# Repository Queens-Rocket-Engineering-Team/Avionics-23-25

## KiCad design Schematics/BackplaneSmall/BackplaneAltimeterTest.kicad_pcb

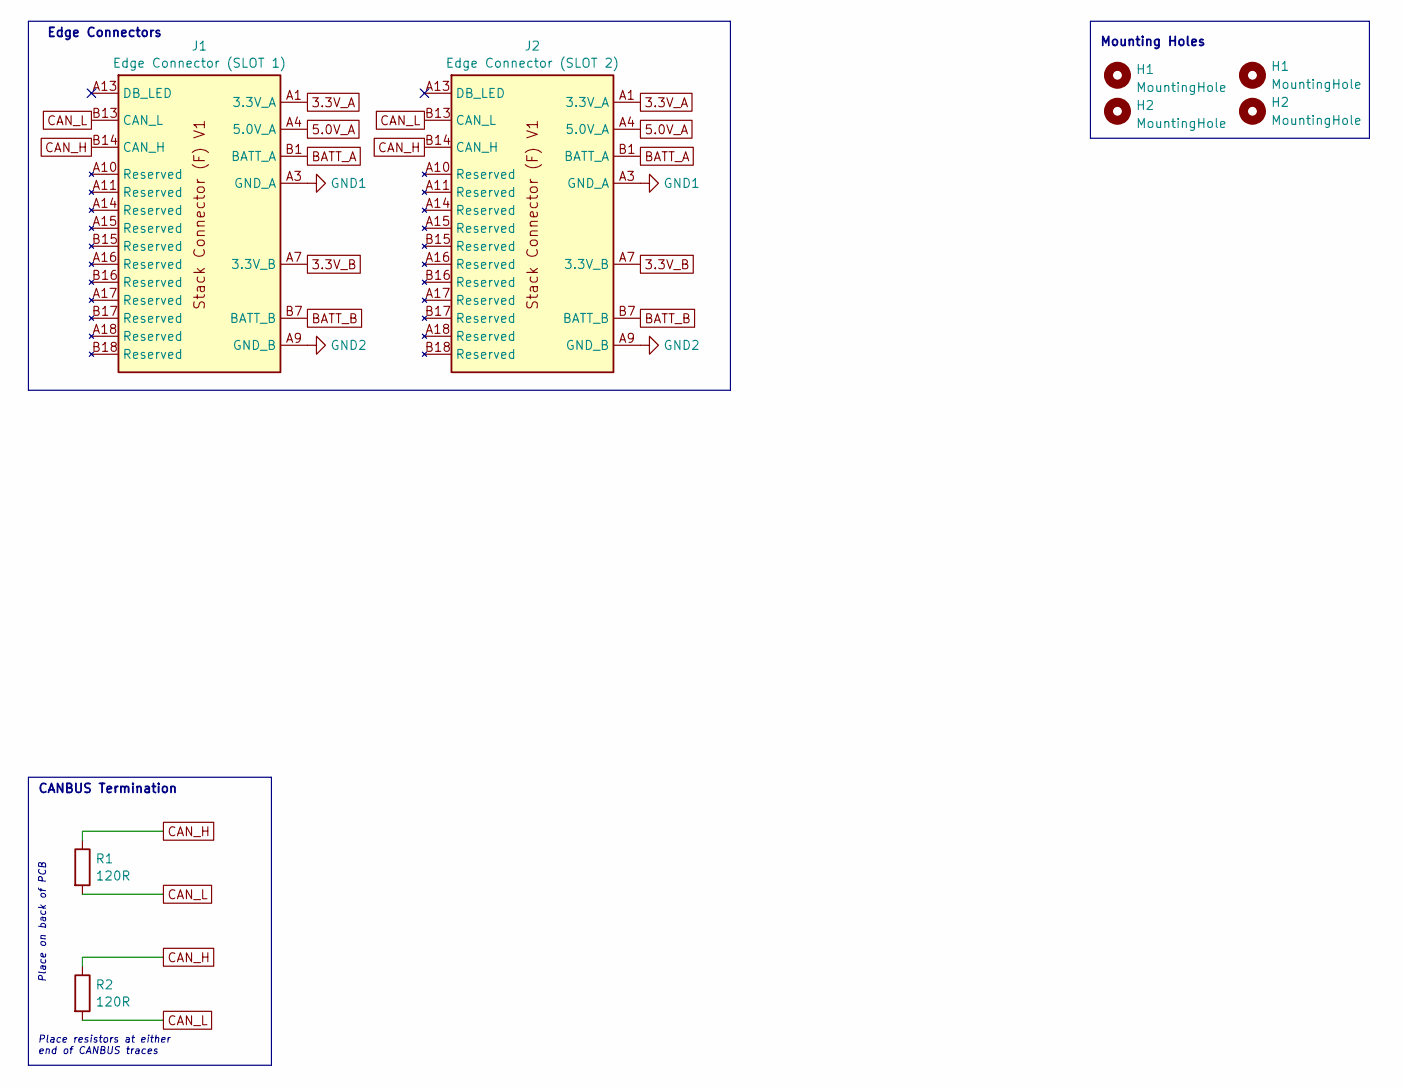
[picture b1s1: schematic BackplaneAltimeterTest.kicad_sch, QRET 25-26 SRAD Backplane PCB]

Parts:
H1, H2: MountingHole; MountingHole_3.2mm_M3_ISO14580_Pad
J1: Edge Connector (SLOT 1); AMPHENOL_10018784-10210TLF; Digikey 609-2029-ND
J2: Edge Connector (SLOT 2); AMPHENOL_10018784-10210TLF; Digikey 609-2029-ND
R1, R2: 120R; R_0805_2012Metric_Pad1.20x1.40mm_HandSolder; Digikey A129738CT-ND

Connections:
3.3V_A: J1.A1 (3.3V_A), J1.A2 (3.3V_A), J2.A1 (3.3V_A), J2.A2 (3.3V_A)
3.3V_B: J1.A7 (3.3V_B), J1.A8 (3.3V_B), J2.A7 (3.3V_B), J2.A8 (3.3V_B)
5.0V_A: J1.A4 (5.0V_A), J1.A5 (5.0V_A), J2.A4 (5.0V_A), J2.A5 (5.0V_A)
BATT_A: J1.B1 (BATT_A), J1.B2 (BATT_A), J1.B3 (BATT_A), J2.B1 (BATT_A), J2.B2 (BATT_A), J2.B3 (BATT_A)
BATT_B: J1.B7 (BATT_B), J1.B8 (BATT_B), J1.B9 (BATT_B), J2.B7 (BATT_B), J2.B8 (BATT_B), J2.B9 (BATT_B)
CAN_H: J1.B14 (CAN_H), J2.B14 (CAN_H), R1.1, R2.1
CAN_L: J1.B13 (CAN_L), J2.B13 (CAN_L), R1.2, R2.2
GND1: J1.A3 (GND_A), J1.A6 (GND_A), J1.B4 (GND_A), J1.B5 (GND_A), J1.B6 (GND_A), J2.A3 (GND_A), J2.A6 (GND_A), J2.B4 (GND_A), J2.B5 (GND_A), J2.B6 (GND_A)
GND2: J1.A9 (GND_B), J1.A12 (GND_B), J1.B10 (GND_B), J1.B11 (GND_B), J1.B12 (GND_B), J2.A9 (GND_B), J2.A12 (GND_B), J2.B10 (GND_B), J2.B11 (GND_B), J2.B12 (GND_B)

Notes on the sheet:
CANBUS Termination
Place resistors at either end of CANBUS traces
Mounting Holes
Edge Connectors
Place on back of PCB

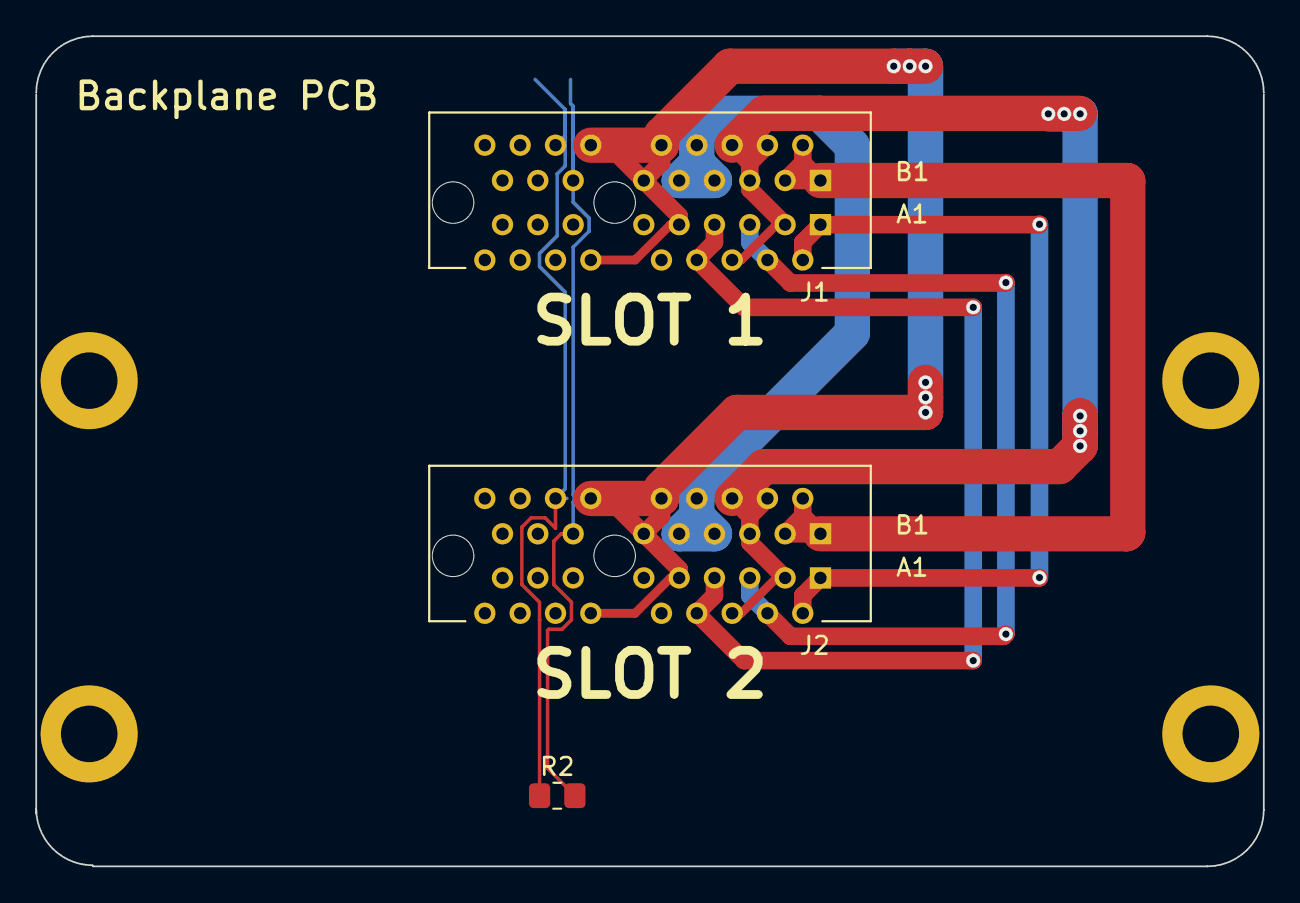
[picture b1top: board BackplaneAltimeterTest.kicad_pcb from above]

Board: 2 copper layers, 69.5 x 47.0 mm, 8 parts (1 on the bottom side), 9 nets.

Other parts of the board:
H3, H4: MountingHole; MountingHole_3.2mm_M3_ISO14580_Pad

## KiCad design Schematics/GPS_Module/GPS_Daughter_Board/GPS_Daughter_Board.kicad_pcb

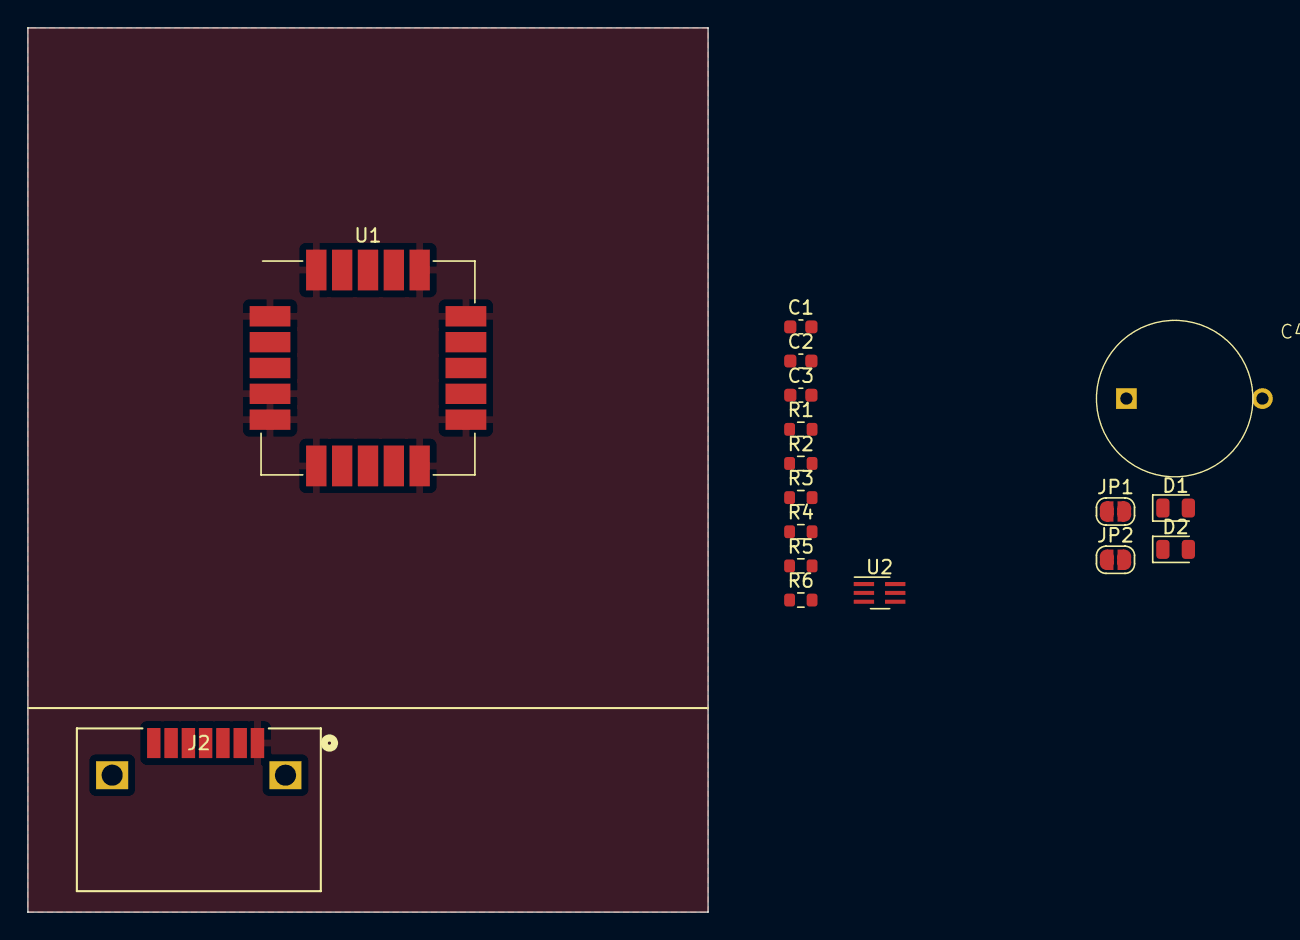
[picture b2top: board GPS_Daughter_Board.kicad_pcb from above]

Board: 2 copper layers, 50.0 x 65.0 mm, 17 parts (0 on the bottom side), 14 nets, no tracks yet.

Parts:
C1, C2: 100nF; C_0603_1608Metric
C3: 1uF; C_0603_1608Metric
C4: 330mF; CB5R5334HF-ZJP
D1: WHITE; LED_0805_2012Metric
D2: GREEN; LED_0805_2012Metric
J2: 470804001; CONN_47080-4001_MOL_SATA
JP1: ENA_PPS_LED; SolderJumper-2_P1.3mm_Open_RoundedPad1.0x1.5mm
JP2: ENA_PWR_LED; SolderJumper-2_P1.3mm_Open_RoundedPad1.0x1.5mm
R1: 10k; R_0603_1608Metric
R2, R3, R4, R5: 2.2k; R_0603_1608Metric
R6: 100R; R_0603_1608Metric
U1: SAM-M10Q; ublox_SAM-M8Q_HandSolder
U2: LM66100DCKR; SC-70-6_Handsoldering

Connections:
3.3V: R1.1, R2.1, R3.2
EXTINT_GPS_D: J2.3, U1.19 (EXTINT)
GPS_3.3V: C1.2, C3.1, J2.2, R5.1, U1.2 (VCC_IO), U1.17 (VCC), U2.1 (VIN)
GPS_BCKP_BATT: C2.2, C4.1, R6.2, U1.3 (V_BCKP)
GPS_GND: C1.1, C2.1, C3.2, C4.2, D1.1 (K), D2.1 (K), J2.1, U1.1 (GND), U1.4 (GND), U1.5 (GND), U1.6 (GND), U1.10 (GND), U1.11 (GND), U1.15 (GND), U1.16 (GND), U1.20 (GND), U2.2 (GND)
unnamed: D1.2 (A), JP1.1 (A)
unnamed: D2.2 (A), JP2.1 (A)
unnamed: JP1.2 (B), R4.2
unnamed: JP2.2 (B), R5.2
unnamed: R6.1, U2.3 (*CE), U2.6 (VOUT)
PPS_GPS_D: J2.7, R4.1, U1.7 (TIMEPULSE)
RST_GPS_D: J2.4, R1.2, U1.18 (~RESET)
SCL_GPS_D: J2.6, R2.2, U1.12 (SCL)
SDA_GPS_D: J2.5, R3.1, U1.9 (SDA)

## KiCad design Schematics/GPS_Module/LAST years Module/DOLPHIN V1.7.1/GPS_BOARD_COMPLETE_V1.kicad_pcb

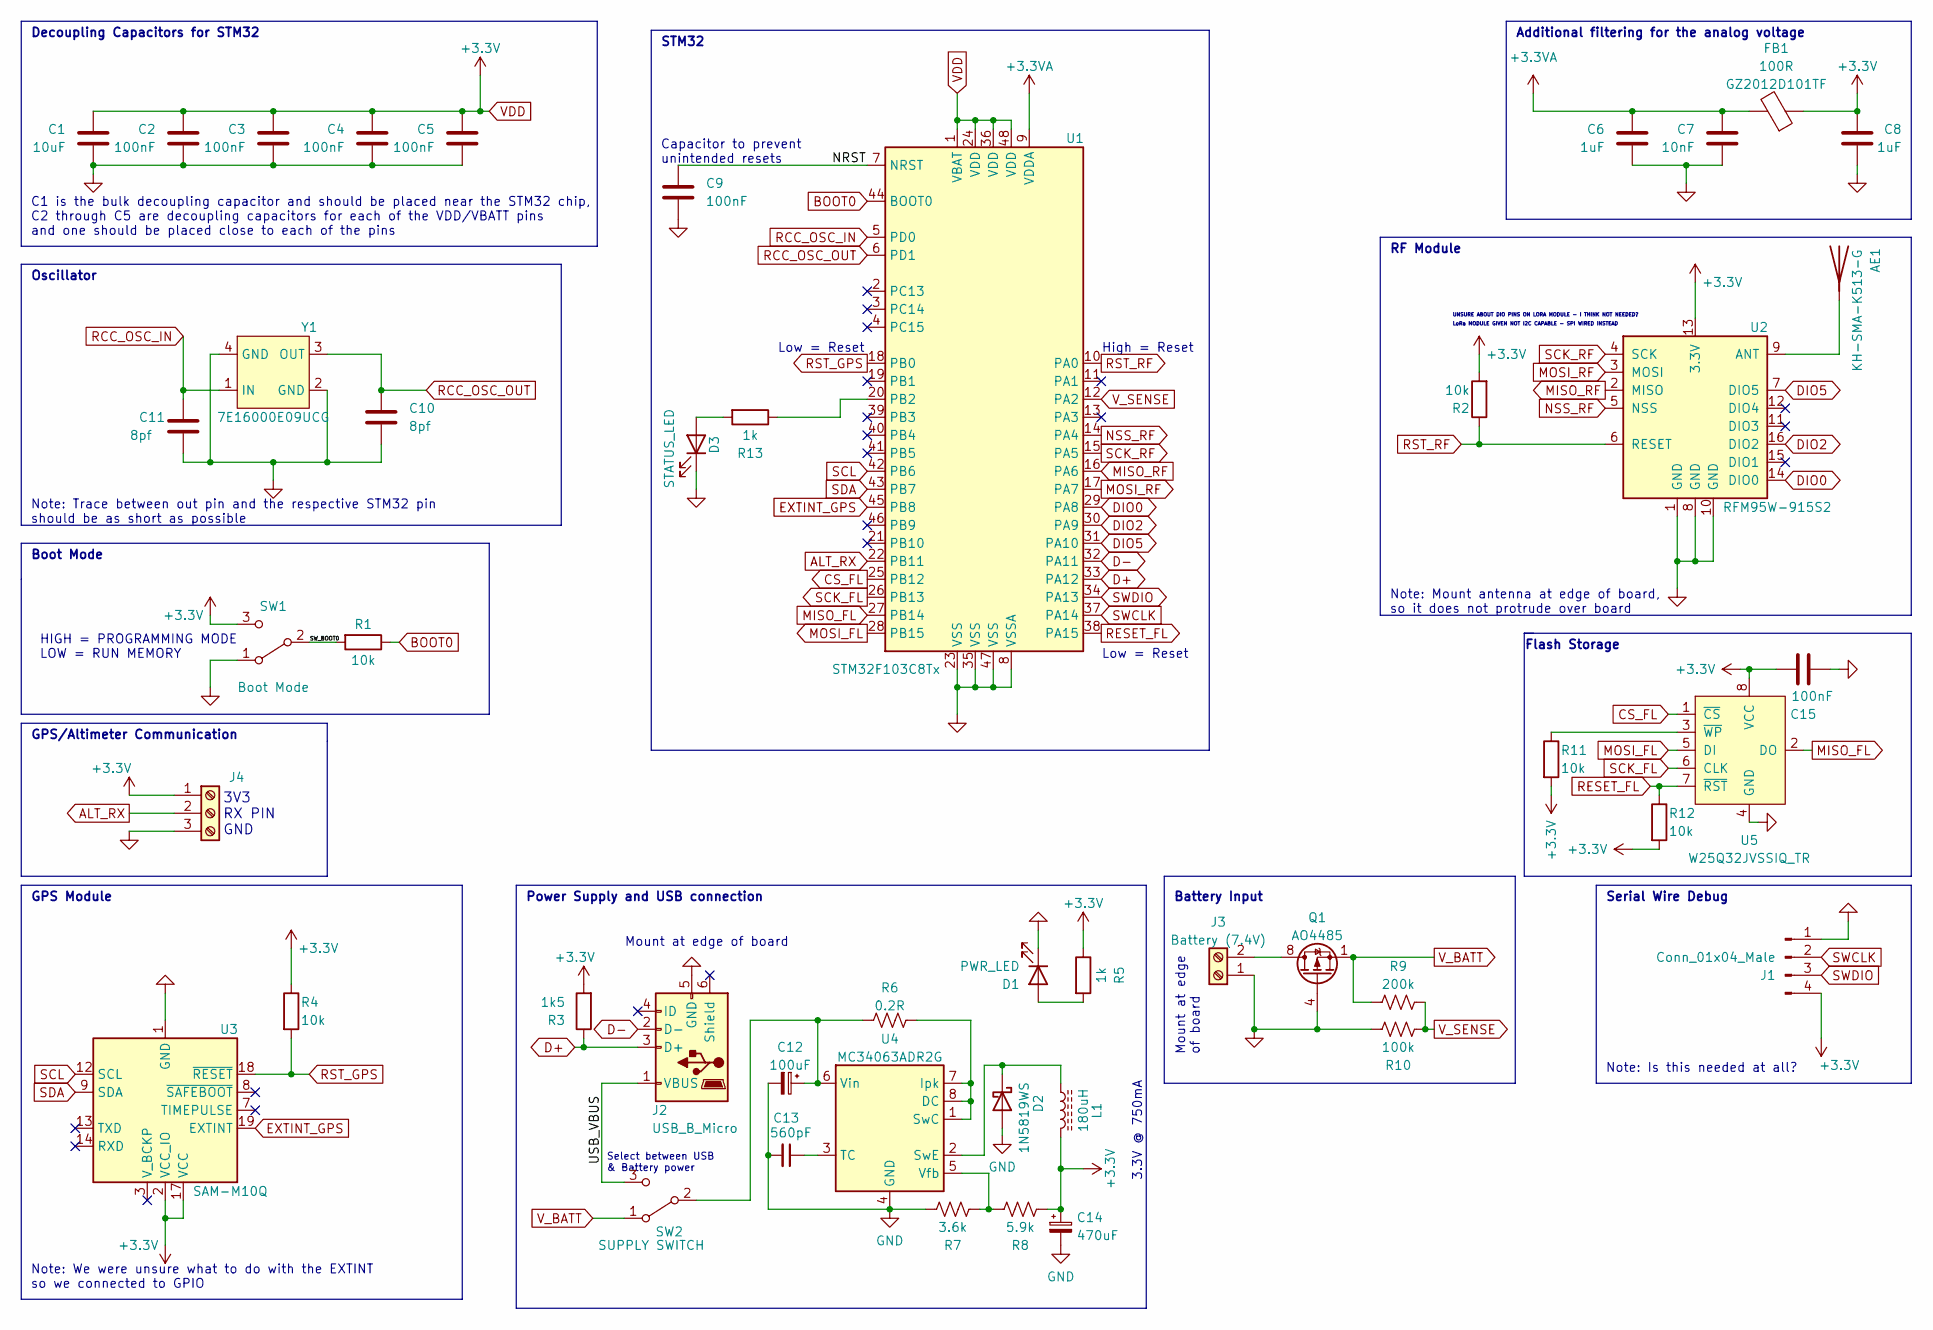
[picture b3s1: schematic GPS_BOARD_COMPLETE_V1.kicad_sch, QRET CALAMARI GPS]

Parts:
AE1: KH-SMA-K513-G; 142-0701-301; LCSC C411575
C1: 10uF; C_Radial_D5.0mm_H11.0mm_P2.00mm
C2, C3, C4, C5, C9: 100nF; C_0805_2012Metric; LCSC C49678
C6, C8: 1uF; C_0603_1608Metric; LCSC C15849
C7: 10nF; C_0402_1005Metric; LCSC C15195
C10, C11: 8pf; C_0402_1005Metric; LCSC C161160
C12: 100uF; C_Radial_D5.0mm_H11.0mm_P2.00mm
C13: 560pF; C_0603_1608Metric; LCSC C458906
C14: 470uF; C_Radial_D6.3mm_H5.0mm_P2.50mm
C15: 100nF; C_0603_1608Metric; LCSC C14663
D1: PWR_LED; LED_0805_2012Metric; LCSC C84256
D2: 1N5819WS; D_SOD-323_HandSoldering; LCSC C191023
D3: STATUS_LED; LED_0805_2012Metric; LCSC C84256
FB1: 100R; L_0805_2012Metric; LCSC C1015
J1: Conn_01x04_Male; PinHeader_1x04_P2.54mm_Vertical
J2: USB_B_Micro; USB_Micro-B_Amphenol_10118194_Horizontal; LCSC C132563
J3: Battery (7.4V); TerminalBlock_Altech_AK300-2_P5.00mm; LCSC C430582
J4: Screw_Terminal_01x03; TerminalBlock_Altech_AK300-3_P5.00mm; LCSC C430584
L1: 180uH; L_TDK_VLP8040; LCSC C96967
Q1: AO4485; SOIC-8_3.9x4.9mm_P1.27mm; LCSC C51499
R1, R2, R4, R11, R12: 10k; R_0603_1608Metric; LCSC C25804
R3: 1k5; R_0603_1608Metric; LCSC C114680
R5, R13: 1k; R_0805_2012Metric; LCSC C17513
R6: 0.2R; R_1206_3216Metric; LCSC C2932839
R7: 3.6k; R_0805_2012Metric; LCSC C228797
R8: 5.9k; R_0805_2012Metric; LCSC C104422
R9: 200k; R_0603_1608Metric; LCSC C25811
R10: 100k; R_0603_1608Metric; LCSC C25803
SW1: Boot Mode; SS-12D07-VG 4 NS GA PA
SW2: SUPPLY SWITCH; SS-12D07-VG 4 NS GA PA
U1: STM32F103C8Tx; LQFP-48_7x7mm_P0.5mm; LCSC C8734
U2: RFM95W-915S2; RFM95W
U3: SAM-M10Q; U-blox_SAM-M8Q
U4: MC34063ADR2G; SOIC-8_3.9x4.9mm_P1.27mm; LCSC C32078
U5: W25Q32JVSSIQ_TR; SOIC-8_W5.6mm; MPN W25Q32JVSSIQ TR; Digi-Key_PN W25Q32JVSSIQCT-ND
Y1: 7E16000E09UCG; Crystal_SMD_2520-4Pin_2.5x2.0mm; LCSC C252260

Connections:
+3.3VA: C6.1, C7.1, FB1.2, U1.9 (VDDA)
/NRST: C9.1, U1.7 (NRST)
/SW_BOOT0: R1.2, SW1.2 (B)
/USB_VBUS: J2.1 (VBUS), SW2.3 (C)
ALT_RX: J4.2, U1.22 (PB11)
BOOT0: R1.1, U1.44 (BOOT0)
CS_FL: U1.25 (PB12), U5.1 (~CS)
D+: J2.3 (D+), R3.1, U1.33 (PA12)
D-: J2.2 (D-), U1.32 (PA11)
DIO0: U1.29 (PA8), U2.14 (DIO0)
DIO2: U1.30 (PA9), U2.16 (DIO2)
DIO5: U1.31 (PA10), U2.7 (DIO5)
EXTINT_GPS: U1.45 (PB8), U3.19 (EXTINT)
GND: C1.2, C2.2, C3.2, C4.2, C5.2, C6.2, C7.2, C8.2, C9.2, C10.2, C11.2, C12.2, C13.2, C14.2, C15.1, D1.1 (K), D2.2 (A), D3.1 (K), J1.1, J2.5 (GND), J3.1, J4.3, Q1.4 (G), R7.1, R10.2, SW1.1 (A), U1.8 (VSSA), U1.23 (VSS), U1.35 (VSS), U1.47 (VSS), U2.1 (GND), U2.8 (GND), U2.10 (GND), U3.1 (GND), U3.4 (GND), U3.5 (GND), U3.6 (GND), U3.10 (GND), U3.11 (GND), U3.15 (GND), U3.16 (GND), U3.20 (GND), U4.4 (GND), U5.4 (GND), Y1.2 (GND), Y1.4 (GND)
MISO_FL: U1.27 (PB14), U5.2 (DO)
MISO_RF: U1.16 (PA6), U2.2 (MISO)
MOSI_FL: U1.28 (PB15), U5.5 (DI)
MOSI_RF: U1.17 (PA7), U2.3 (MOSI)
NSS_RF: U1.14 (PA4), U2.5 (NSS)
unnamed: AE1.1 (A), U2.9 (ANT)
unnamed: C12.1, R6.2, SW2.2 (B), U4.6 (Vin)
unnamed: C13.1, U4.3 (TC)
unnamed: D1.2 (A), R5.2
unnamed: D2.1 (K), L1.1, U4.2 (SwE)
unnamed: D3.2 (A), R13.2
unnamed: J3.2, Q1.5 (D), Q1.6 (D), Q1.7 (D), Q1.8 (D)
unnamed: R6.1, U4.1 (SwC), U4.7 (Ipk), U4.8 (DC)
unnamed: R7.2, R8.2, U4.5 (Vfb)
unnamed: R11.1, U5.3 (~WP)
unnamed: R13.1, U1.20 (PB2)
RCC_OSC_IN: C11.1, U1.5 (PD0), Y1.1 (IN)
RCC_OSC_OUT: C10.1, U1.6 (PD1), Y1.3 (OUT)
RESET_FL: R12.1, U1.38 (PA15), U5.7 (~RST)
RST_GPS: R4.2, U1.18 (PB0), U3.18 (~RESET)
RST_RF: R2.1, U1.10 (PA0), U2.6 (RESET)
SCK_FL: U1.26 (PB13), U5.6 (CLK)
SCK_RF: U1.15 (PA5), U2.4 (SCK)
SCL: U1.42 (PB6), U3.12 (SCL)
SDA: U1.43 (PB7), U3.9 (SDA)
SWCLK: J1.2, U1.37 (PA14)
SWDIO: J1.3, U1.34 (PA13)
VDD: C1.1, C2.1, C3.1, C4.1, C5.1, C8.1, C14.1, C15.2, FB1.1, J1.4, J4.1, L1.2, R2.2, R3.2, R4.1, R5.1, R8.1, R11.2, R12.2, SW1.3 (C), U1.1 (VBAT), U1.24 (VDD), U1.36 (VDD), U1.48 (VDD), U2.13 (3.3V), U3.2 (VCC_IO), U3.17 (VCC), U5.8 (VCC)
V_BATT: Q1.1 (S), Q1.2 (S), Q1.3 (S), R9.2, SW2.1 (A)
V_SENSE: R9.1, R10.1, U1.12 (PA2)

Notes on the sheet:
Battery Input
STM32
Note: Is this needed at all?
Power Supply and USB connection
Additional filtering for the analog voltage
3V3 RX PIN GND
Low = Reset
Serial Wire Debug
UNSURE ABOUT DIO PINS ON LORA MODULE - I THINK NOT NEEDED?
GPS/Altimeter Communication
Capacitor to prevent unintended resets
RF Module
C1 is the bulk decoupling capacitor and should be placed near the STM32 chip, C2 through C5 are decoupling capacitors for each of the VDD/VBATT pins and one should be placed close to each of the pins
Decoupling Capacitors for STM32
Note: We were unsure what to do with the EXTINT so we connected to GPIO
Note: Trace between out pin and the respective STM32 pin should be as short as possible
Note: Mount antenna at edge of board, so it does not protrude over board
High = Reset
Boot Mode
Mount at edge of board
Oscillator
GPS Module
Select between USB & Battery power
3.3V @ 750mA
Mount at edge of board
HIGH = PROGRAMMING MODE LOW = RUN MEMORY
Flash Storage
LoRa MODULE GIVEN NOT I2C CAPABLE - SPI WIRED INSTEAD

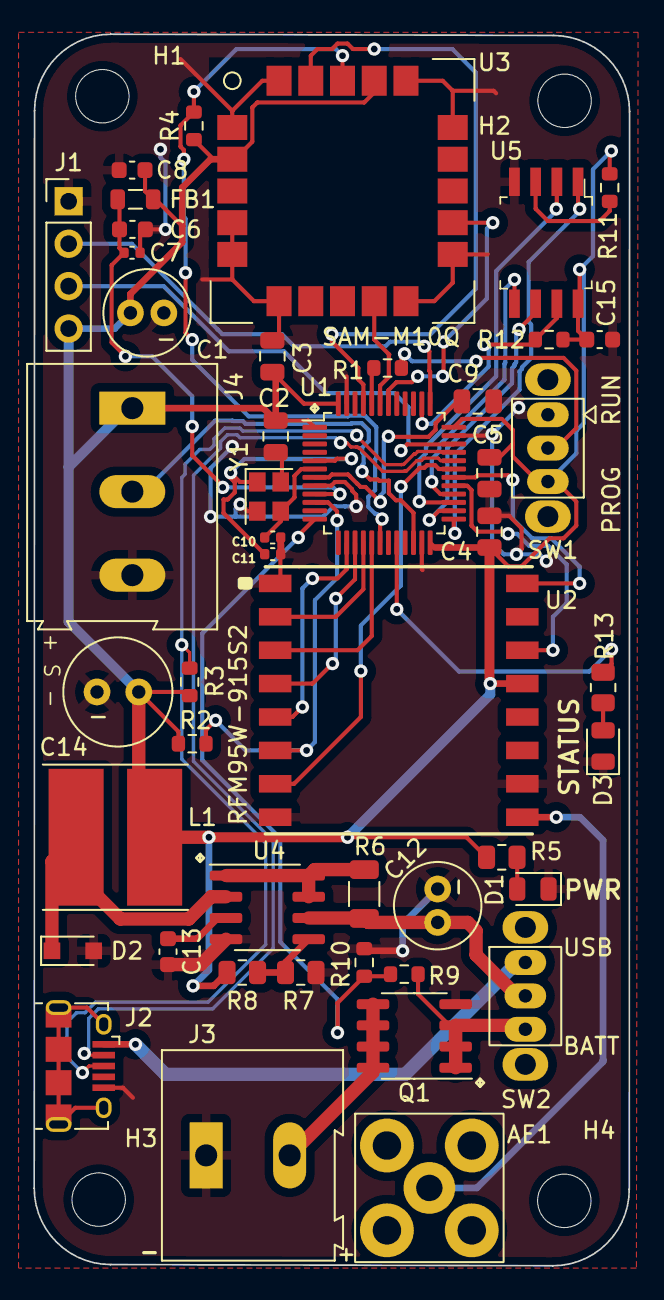
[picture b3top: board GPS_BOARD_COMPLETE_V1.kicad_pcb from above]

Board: 2 copper layers, 35.7 x 73.7 mm, 51 parts (0 on the bottom side), 44 nets.

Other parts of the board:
H1, H2, H3, H4: MountingHole_3.2mm_M3

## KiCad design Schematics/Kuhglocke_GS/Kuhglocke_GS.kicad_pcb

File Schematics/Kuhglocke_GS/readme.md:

# Kuhglocke Portable Ground Station

This directory contains the V1.0 revision of the Kuhglocke ground station. It has several known problems;

### Critical Problems
- VSS/VDD pins are reversed on the SD card. This results in immediately destroying the MicroSD card. Swap pins to fix.
- NAU7802 ADC range is half of expected; change R17 to 20k to allow battery measurement.
- The CP2012's reset pullUP resistor (R29) is erroneously connected to GND, prevents it from functioning. Change to pullup to fix.
- The 5V disabling the Buck-Boost PSU causes brownouts (circuit around Q6); redesign circuit or remove function to fix.

### Future Suggestions
- YIC31616 GPS module should have a V_BCKP source (TTFF is very slow)
- The NAU7802 ADC is slow & difficult to work with; switch to something else
- Look into using the MAX17043 for battery management
- Look into using TP4056 for battery charging (cheaper)

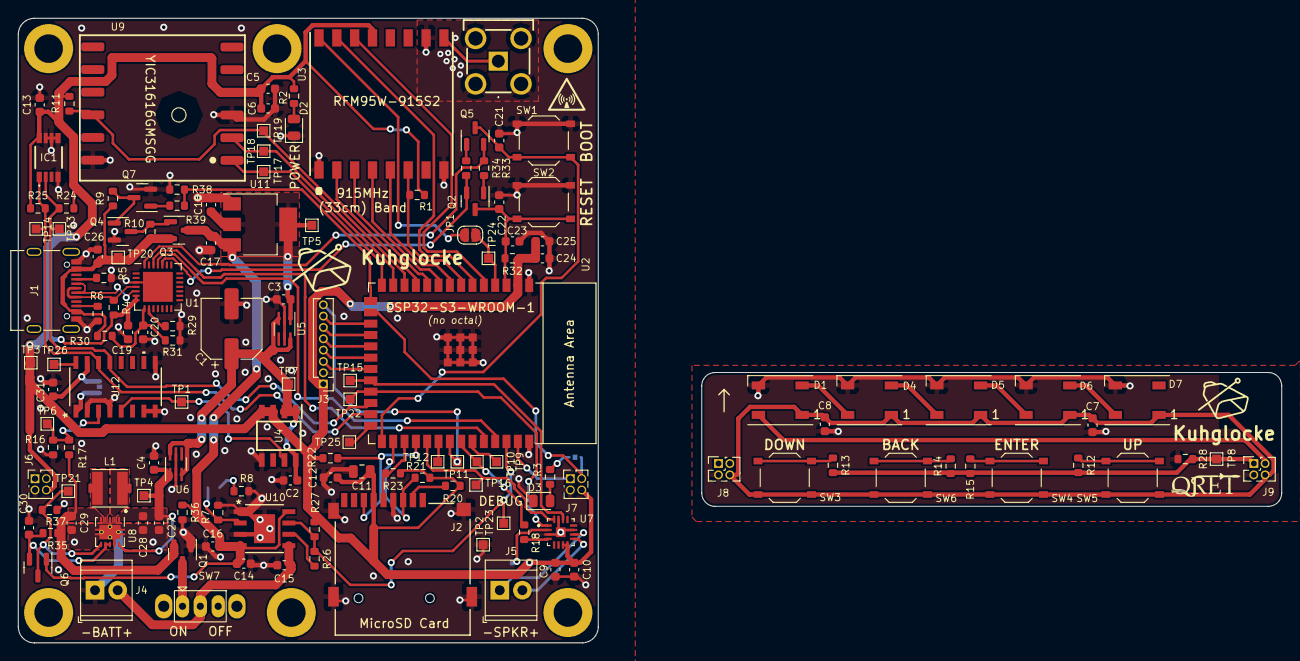
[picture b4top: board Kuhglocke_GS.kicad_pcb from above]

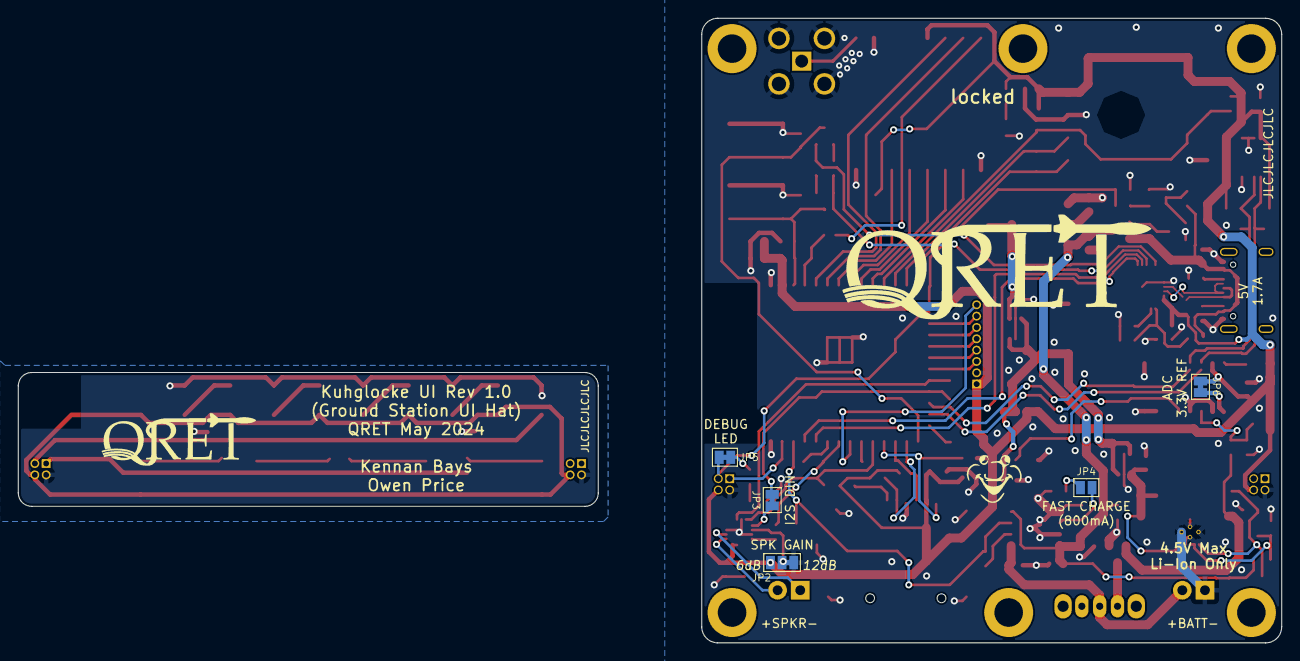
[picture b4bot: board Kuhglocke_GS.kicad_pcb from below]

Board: 2 copper layers, 65.0 x 70.0 mm, 152 parts (5 on the bottom side), 94 nets.

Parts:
AE1: Antenna; PCB114SMAFRAJA
C1: 100uF; CP_Elec_6.3x5.9
C2, C5, C9, C12, C13, C16, C21, C22, C25, C30: 0.1uF; C_0603_1608Metric
C3, C4, C7, C8, C14, C15, C20, C23, C31: 1uF; C_0603_1608Metric
C6: 4.7uF; C_0603_1608Metric
C10, C17, C18, C19, C24, C26, C27, C28, C29: 10uF; C_0603_1608Metric
C11: 47uF; C_0805_2012Metric
D1, D4, D5, D6, D7: WS2812B; LED_WS2812B_PLCC4_5.0x5.0mm_P3.2mm
D2: INT_PWR_LED (RED); LED_0805_2012Metric
D3: DB_LED (GRN); LED_0805_2012Metric
H1, H2, H3, H4, H5, H6: MountingHole; MountingHole_3.2mm_M3_ISO14580_Pad
IC1: P3T1755DPZ
J1: USB_C_Female_USB2_Small; USB_C_DB-108PWB
J2: MSD-1-A MicroSD Slot; MicroSD_MSD-1-A
J3: PinHeader_1x08_P1.27mm_Vertical
J4: 1S Li-Ion Cell; TerminalBlock_TE_282834-2_1x02_P2.54mm_Horizontal
J5: Speaker; TerminalBlock_TE_282834-2_1x02_P2.54mm_Horizontal
J6: MB_A; PinSocket_2x02_P1.27mm_Vertical
J7: MB_B; PinSocket_2x02_P1.27mm_Vertical
J8: DB_A; HPH2-A-04-UA_PINS
J9: DB_B; HPH2-A-04-UA_PINS
JP1: DIO2_EN; SolderJumper-2_P1.3mm_Open_RoundedPad1.0x1.5mm
JP2: Gain; SolderJumper-3_P1.3mm_Bridged12_Pad1.0x1.5mm_NumberLabels
JP3: SPK_DIN; SolderJumper-2_P1.3mm_Bridged_Pad1.0x1.5mm
JP4: FastCharge; SolderJumper-2_P1.3mm_Open_Pad1.0x1.5mm
JP5: DB_LED_EN; SolderJumper-2_P1.3mm_Bridged_Pad1.0x1.5mm
JP6: ADC_REFP; SolderJumper-2_P1.3mm_Bridged_Pad1.0x1.5mm
L1: 2.2uH; L_Taiyo-Yuden_MD-4040
Q1, Q3, Q6: AO3401A; SOT-23
Q2, Q5: MMBT3904; SOT-23
Q4, Q7: AO3400A; SOT-23
R1, R3, R11, R16, R17, R20, R21, R22, R23, R26, R27, R32, R33, R34: 10k; R_0603_1608Metric
R2: 1.8k; R_0603_1608Metric
R4: 1.5k; R_0603_1608Metric
R5, R6: 5.1k; R_0603_1608Metric
R7: 2.4k; R_0603_1608Metric
R8: 3.9k; R_0603_1608Metric
R9, R18, R36, R38: 100k; R_0603_1608Metric
R10, R37: 51k; R_0603_1608Metric
R12, R39: 510; R_0603_1608Metric
R13, R28, R29: 1k; R_0603_1608Metric
R14: 2k; R_0603_1608Metric
R15: 5.6k; R_0603_1608Metric
R24, R25: 4.7k; R_0603_1608Metric
R30: 22k; R_0603_1608Metric
R31: 47k; R_0603_1608Metric
R35: 100; R_0603_1608Metric
SW1: SW_ESP_BOOT_MODE; SW_Push_1P1T_XKB_TS-1187A
SW2: SW_ESP_RESET; SW_Push_1P1T_XKB_TS-1187A
SW3: SW_DOWN; SW_Push_1P1T_XKB_TS-1187A
SW4: SW_ENTER; SW_Push_1P1T_XKB_TS-1187A
SW5: SW_UP; SW_Push_1P1T_XKB_TS-1187A
SW6: SW_BACK; SW_Push_1P1T_XKB_TS-1187A
SW7: PWR; SS-12D07-VG 4 NS GA PA
TP1: TP_ISENSE; TestPoint_Pad_1.0x1.0mm
TP2: TP_GND; TestPoint_Pad_1.0x1.0mm
TP3: TP_3V3; TestPoint_Pad_1.0x1.0mm
TP4: TP_VPSU; TestPoint_Pad_1.0x1.0mm
TP5: TP_VUSB; TestPoint_Pad_1.0x1.0mm
TP6: B_SENSE; TestPoint_Pad_1.0x1.0mm
TP7: TP_MUX; TestPoint_Pad_1.0x1.0mm
TP8: TP_BTN; TestPoint_Pad_1.0x1.0mm
TP9: IO42; TestPoint_Pad_1.0x1.0mm
TP10: IO41; TestPoint_Pad_1.0x1.0mm
TP11: IO40; TestPoint_Pad_1.0x1.0mm
TP12: IO39; TestPoint_Pad_1.0x1.0mm
TP13: TP_SCL; TestPoint_Pad_1.0x1.0mm
TP14: TP_SDA; TestPoint_Pad_1.0x1.0mm
TP15: I2S_LRCLK; TestPoint_Pad_1.0x1.0mm
TP16: I2S_BLCK; TestPoint_Pad_1.0x1.0mm
TP17: GPS_RX; TestPoint_Pad_1.0x1.0mm
TP18: GPS_TX; TestPoint_Pad_1.0x1.0mm
TP19: GPS_RST; TestPoint_Pad_1.0x1.0mm
TP20: 5V_RAW; TestPoint_Pad_1.0x1.0mm
TP21: PSU_EN; TestPoint_Pad_1.0x1.0mm
TP22: I2S_DIN; TestPoint_Pad_1.0x1.0mm
TP23: CHRG_STAT; TestPoint_Pad_1.0x1.0mm
TP24: IO4; TestPoint_Pad_1.0x1.0mm
TP25: IO45; TestPoint_Pad_1.0x1.0mm
TP26: ADC_LDO; TestPoint_Pad_1.0x1.0mm
U1: CP2102N-Axx-xQFN28; QFN-28-1EP_5x5mm_P0.5mm_EP3.35x3.35mm
U2: ESP32-S3-WROOM-1
U3: RFM95W-915S2; RFM95W
U4: ACS70331EOLC; SOIC127P600X175-8N
U5, U6: LM66100DCKR; SC-70-6_Handsoldering
U7: MAX98357AETE_T; MAX98357_QFN50P300X300X80-17N
U8: TPS63001DRCR; Texas_DRC0010J_ThermalVias
U9: YIC31616GMSGG GPS; YIC31616GMSGG
U10: TPB4056B2X-ES1R; ES1ESOP-8-F_TPK
U11: AMS1117-3.3; SOT-223-3_TabPin2
U12: NAU7802SGI; SOI16_NAU7802SGI_NUV

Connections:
5V_OFF: R38.1, R39.1, U2.15 (GPIO3/TOUCH3/ADC1_CH2)
5V_RAW: C26.2, J1.A4 (VBUS), J1.A9 (VBUS), J1.B4 (VBUS), J1.B9 (VBUS), Q3.2 (S), R9.1, R10.1, R30.2, TP20.1
+3.3V: C5.2, C6.2, C9.1, C10.1, C11.1, C12.1, C13.1, C19.2, C24.1, C25.1, C31.2, IC1.8 (VCC), J2.6 (VSS), J3.1 (VCC), J6.4, J7.4, JP2.3 (B), JP6.1 (A), R1.2, R2.2, R4.2, R11.1, R20.1, R21.1, R22.1, R23.1, R24.2, R25.1, R27.2, R32.1, TP3.1, U1.6 (VDD), U1.7 (VREGIN), U2.2 (3V3), U3.13 (3.3V), U4.3 (IP-), U4.4 (IP-), U7.7 (VDD), U7.8 (VDD__1), U9.4 (VCC), U12.15 (DVDD)
+3.3VA: C7.2, C8.2, D1.1 (VDD), D4.1 (VDD), D5.1 (VDD), D6.1 (VDD), D7.1 (VDD), J8.4, J9.4, SW3.1, SW4.1, SW5.1, SW6.1
+5V: C14.1, C16.2, C17.1, Q3.3 (D), Q6.1 (G), R36.1, U10.4 (VIN), U10.8 (CE), U11.3 (VI)
+BATT: C29.1, Q1.2 (S), R17.1, R35.1, U8.5 (VIN)
/LA: L1.2, U8.2 (L2)
/LB: L1.1, U8.4 (L1)
ARGB_DATA: J7.3, JP5.1 (A), U2.16 (GPIO46)
ARGB_DATA_DB: D1.4 (DIN), J9.3
BATT_SENSE: R16.1, R17.2, TP6.1, U12.3 (VIN1P)
BUTTONS: J7.1, U2.39 (GPIO1/TOUCH1/ADC1_CH0)
BUTTONS_DB: J9.1, R12.2, R13.2, R14.1, R15.2, R28.2, TP8.1
CHRG_STAT: R26.2, R27.1, TP23.1, U2.38 (GPIO2/TOUCH2/ADC1_CH1), U10.7 (CHRG)
CLK_SDMMC: J2.5 (CLK), R23.2, U2.29 (SPIIO7/GPIO36/FSPICLK/SUBSPICLK)
CMD_SDMMC: J2.3 (CMD), R21.2, U2.28 (SPIIO6/GPIO35/FSPID/SUBSPID)
CS_EINK: J3.5 (CS), U2.19 (GPIO11/TOUCH11/ADC2_CH0/FSPID/FSPIIO5/S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)
CS_RF: U2.8 (GPIO15/U0RTS/ADC2_CH4/XTAL_32K_P), U3.5 (NSS)
CURR_SENSE: TP1.1, U4.7 (VOUT), U12.5 (VIN2P)
D0_SDMMC: J2.7 (DAT0), R22.2, U2.30 (SPIDQS/GPIO37/FSPIQ/SUBSPIQ)
DIO0_RF: U2.5 (GPIO5/TOUCH5/ADC1_CH4), U3.14 (DIO0)
DIO1_RF: U2.6 (GPIO6/TOUCH6/ADC1_CH5), U3.15 (DIO1)
DIO2_RF: JP1.2 (B), TP24.1, U2.4 (GPIO4/TOUCH4/ADC1_CH3)
DTR: Q5.2 (E), R33.1, U1.28 (~DTR)
EINK_BUSY: J3.8 (BUSY), TP11.1, U2.33 (MTDO/GPIO40/CLK_OUT2)
EINK_DC: J3.6 (DC), U2.18 (GPIO10/TOUCH10/ADC1_CH9/FSPICS0/FSPIIO4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)
ESP32_EN: C22.2, C23.2, Q2.3 (C), R32.2, SW2.2, U2.3 (EN)
GND: AE1.2 (Shield), C1.2, C2.2, C3.2, C4.2, C5.1, C6.1, C9.2, C10.2, C11.2, C12.2, C13.2, C14.2, C15.1, C16.1, C17.2, C18.2, C19.1, C20.1, C21.1, C22.1, C23.1, C24.2, C25.2, C26.1, C27.2, C28.2, C29.2, C30.2, C31.1, D2.1 (K), D3.1 (K), IC1.4 (GND), IC1.5 (A2), IC1.6 (A1), IC1.7 (A0), J1.A1 (GND), J1.A12 (GND), J1.B1 (GND), J1.B12 (GND), J2.4 (VDD), J2.10 (SHIELD), J3.2 (GND), J4.1, J6.2, J7.2, JP2.1 (A), Q1.1 (G), Q4.2 (S), Q7.2 (S), R5.2, R6.2, R7.1, R8.2, R16.2, R29.2, R31.1, R36.2, R37.1, R38.2, SW1.1, SW2.1, TP2.1, U1.3 (GND), U1.29 (GND), U2.1 (GND), U2.40 (GND), U2.41 (GND), U3.1 (GND), U3.8 (GND), U3.10 (GND), U4.5 (GND), U5.2 (GND), U5.5 (ST), U6.2 (GND), U6.5 (ST), U7.3 (GND), U7.11 (GND__1), U7.15 (GND__2), U7.17 (EP), U8.3 (PGND), U8.9 (GND), U8.11 (PGND), U9.3 (GND), U9.12 (GND), U10.1 (TEMP), U10.3 (GND), U10.9 (GND), U11.1 (GND), U12.2 (VIN1N), U12.4 (VIN2N), U12.7 (REFN), U12.8 (AVSS), U12.9 (DVSS)
GND2: C7.1, C8.1, D1.3 (VSS), D4.3 (VSS), D5.3 (VSS), D6.3 (VSS), D7.3 (VSS), J8.2, J9.2, R28.1
GPIO0: C21.2, Q5.3 (C), SW1.2, U2.27 (GPIO0/BOOT)
GPS_RST: R11.2, TP19.1, U2.12 (GPIO8/TOUCH8/ADC1_CH7/SUBSPICS1), U9.10 (RESET)
I2C_SCL: IC1.2 (SCL), R24.1, TP13.1, U2.24 (GPIO47/SPICLK_P/SUBSPICLK_P_DIFF), U12.13 (SCLK)
I2C_SDA: IC1.1 (SDA), R25.2, TP14.1, U2.25 (GPIO48/SPICLK_N/SUBSPICLK_N_DIFF), U12.14 (SDIO)
I2S_BCLK_SPK: TP16.1, U2.31 (GPIO38/FSPIWP/SUBSPIWP), U7.16 (BCLK)
I2S_DIN_SPK: JP3.2 (B), TP22.1, U2.23 (GPIO21)
I2S_LRCLK_SPK: TP15.1, U2.22 (GPIO14/TOUCH14/ADC2_CH3/FSPIWP/FSPIDQS/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), U7.14 (LRCLK)
MISO_EINK: TP9.1, U2.35 (MTMS/GPIO42)
MISO_RF: U2.11 (GPIO18/U1RXD/ADC2_CH7/CLK_OUT3), U3.2 (MISO)
MOSI_EINK: J3.3 (DIN), U2.21 (GPIO13/TOUCH13/ADC2_CH2/FSPIQ/FSPIIO7/S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)
MOSI_RF: U2.10 (GPIO17/U1TXD/ADC2_CH6), U3.3 (MOSI)
unnamed: AE1.1 (A), U3.9 (ANT)
unnamed: D1.2 (DOUT), D4.4 (DIN)
unnamed: D2.2 (A), R2.1
unnamed: D3.2 (A), R3.1
unnamed: D4.2 (DOUT), D5.4 (DIN)
unnamed: D5.2 (DOUT), D6.4 (DIN)
unnamed: D6.2 (DOUT), D7.4 (DIN)
unnamed: J1.A5 (CC1), R5.1
unnamed: J1.B5 (CC2), R6.1
unnamed: J2.2 (DAT3/CD), R20.2
unnamed: J5.1, U7.10 (OUTN)
unnamed: J5.2, U7.9 (OUTP)
unnamed: JP1.1 (A), U3.16 (DIO2)
unnamed: JP2.2 (C), U7.2 (GAIN_SLOT)
unnamed: JP3.1 (A), U7.1 (DIN)
unnamed: JP4.1 (A), R8.1
unnamed: JP4.2 (B), R7.2, U10.2 (PROG)
unnamed: JP5.2 (B), R3.2
unnamed: JP6.2 (B), U12.1 (REFP)
unnamed: Q1.3 (D), SW7.1 (A)
unnamed: Q2.1 (B), R33.2
unnamed: Q3.1 (G), Q4.3 (D), R10.2
unnamed: Q4.1 (G), Q7.3 (D), R9.2
unnamed: Q5.1 (B), R34.1
unnamed: Q6.3 (D), R37.2, TP21.1, U8.6 (EN)
unnamed: C30.1, Q6.2 (S), R35.2, U8.7 (PS/SYNC), U8.8 (VINA)
unnamed: Q7.1 (G), R39.2
unnamed: R12.1, SW5.2
unnamed: R13.1, SW3.2
unnamed: R14.2, SW6.2
unnamed: R15.1, SW4.2
unnamed: C20.2, R30.1, R31.2, U1.8 (VBUS)
unnamed: R29.1, U1.9 (~RST)
unnamed: TP25.1, U2.26 (GPIO45)
unnamed: TP12.1, U2.32 (MTCK/GPIO39/CLK_OUT3/SUBSPICS1)
unnamed: R18.2, U7.4 (SD_MODE)
unnamed: R26.1, U10.6 (STBY)
unnamed: TP26.1, U12.16 (AVDD/LDO)
RAW_BATT: C15.2, J4.2, SW7.2 (B), U10.5 (BAT)
RESET_EINK: J3.7 (RST), U2.17 (GPIO9/TOUCH9/ADC1_CH8/FSPIHD/SUBSPIHD)
RESET_RF: R1.1, U2.7 (GPIO7/TOUCH7/ADC1_CH6), U3.6 (RESET)
RTS: Q2.2 (E), R34.2, U1.24 (~RTS)
SCK_EINK: J3.4 (CLK), U2.20 (GPIO12/TOUCH12/ADC2_CH1/FSPICLK/FSPIIO6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)
SCK_RF: U2.9 (GPIO16/U0CTS/ADC2_CH5/XTAL_32K_N), U3.4 (SCK)
SPK_ON: R18.1, TP10.1, U2.34 (MTDI/GPIO41/CLK_OUT1)
UART0_RX: U1.26 (TXD), U2.36 (U0RXD/GPIO44/CLK_OUT2)
UART0_TX: U1.25 (RXD), U2.37 (U0TXD/GPIO43/CLK_OUT1)
UART1_GPS_RX: TP18.1, U2.13 (GPIO19/U1RTS/ADC2_CH8/CLK_OUT2/USB_D-), U9.2 (TXD)
UART1_GPS_TX: TP17.1, U2.14 (GPIO20/U1CTS/ADC2_CH9/CLK_OUT1/USB_D+), U9.1 (RXD)
USB_D+: J1.A6 (D+), J1.B6 (D+), R4.1, U1.4 (D+)
USB_D-: J1.A7 (D-), J1.B7 (D-), U1.5 (D-)
V_MUX: C1.1, C2.1, TP7.1, U4.1 (IP+), U4.2 (IP+), U4.8 (VCC), U5.3 (*CE), U5.6 (VOUT), U6.3 (*CE), U6.6 (VOUT)
V_PSU: C4.1, C27.1, C28.1, TP4.1, U6.1 (VIN), U8.1 (VOUT), U8.10 (FB)
V_REGUSB: C3.1, C18.1, TP5.1, U5.1 (VIN), U11.2 (VO)
